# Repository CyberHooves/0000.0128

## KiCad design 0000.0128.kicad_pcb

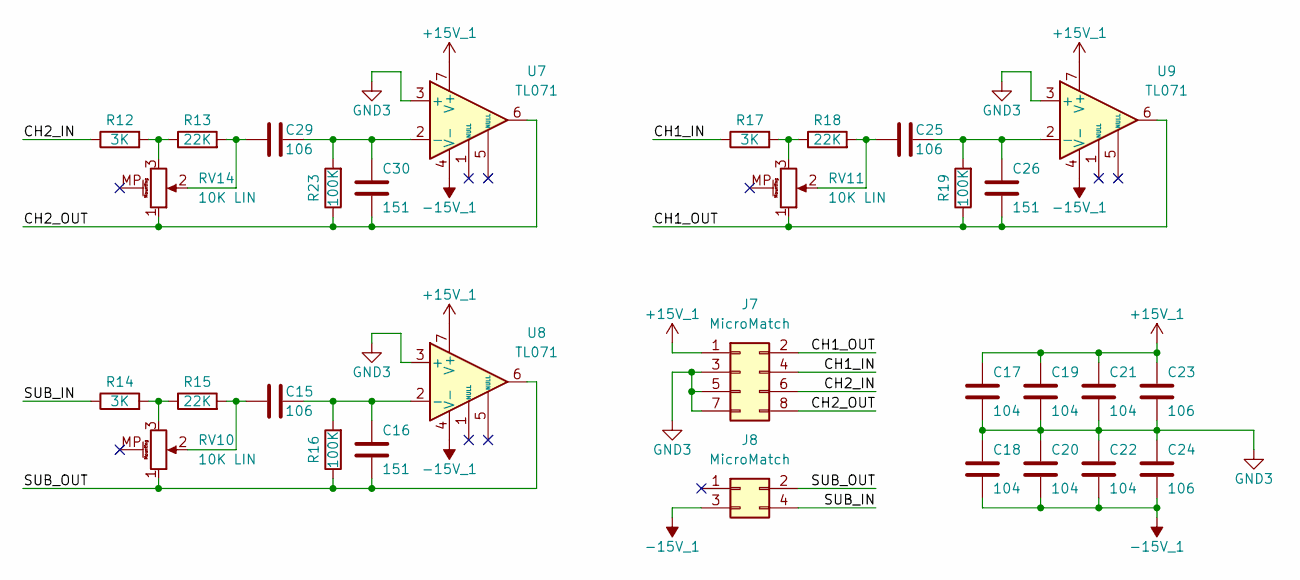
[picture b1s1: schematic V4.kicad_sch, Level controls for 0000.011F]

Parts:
C15, C23, C24, C25, C29: 106; C_1210_3225Metric
C16, C26, C30: 151; C_0805_2012Metric
C17, C18, C19, C20, C21, C22: 104; C_0805_2012Metric
J7: MicroMatch; TE_Micro-MaTch_215079-8_2x04_P1.27mm_Vertical
J8: MicroMatch; TE_Micro-MaTch_215079-4_2x02_P1.27mm_Vertical
R12, R14, R17: 3K; R_0805_2012Metric
R13, R15, R18: 22K; R_0805_2012Metric
R16, R19, R23: 100K; R_0805_2012Metric
RV10, RV11, RV14: 10K LIN; Potentiometer_Alps_RK09L_Single_Vertical
U7, U8, U9: TL071; SOIC-8_3.9x4.9mm_P1.27mm

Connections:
+15V_1: C17.1, C19.1, C21.1, C23.1, J7.1, U7.7 (V+), U8.7 (V+), U9.7 (V+)
-15V_1: C18.2, C20.2, C22.2, C24.2, J8.3, U7.4 (V-), U8.4 (V-), U9.4 (V-)
/Variant 4/CH1_IN: J7.4, R17.1
/Variant 4/CH1_OUT: C26.2, J7.2, R19.1, RV11.1, U9.6
/Variant 4/CH2_IN: J7.6, R12.1
/Variant 4/CH2_OUT: C30.2, J7.8, R23.1, RV14.1, U7.6
/Variant 4/SUB_IN: J8.4, R14.1
/Variant 4/SUB_OUT: C16.2, J8.2, R16.1, RV10.1, U8.6
GND3: C17.2, C18.1, C19.2, C20.1, C21.2, C22.1, C23.2, C24.1, J7.3, J7.5, J7.7, U7.3 (+), U8.3 (+), U9.3 (+)
unnamed: C15.1, R15.2, RV10.2
unnamed: C25.1, R18.2, RV11.2
unnamed: C29.1, R13.2, RV14.2
unnamed: R12.2, R13.1, RV14.3
unnamed: R14.2, R15.1, RV10.3
unnamed: R17.2, R18.1, RV11.3
unnamed: C29.2, C30.1, R23.2, U7.2 (-)
unnamed: C15.2, C16.1, R16.2, U8.2 (-)
unnamed: C25.2, C26.1, R19.2, U9.2 (-)

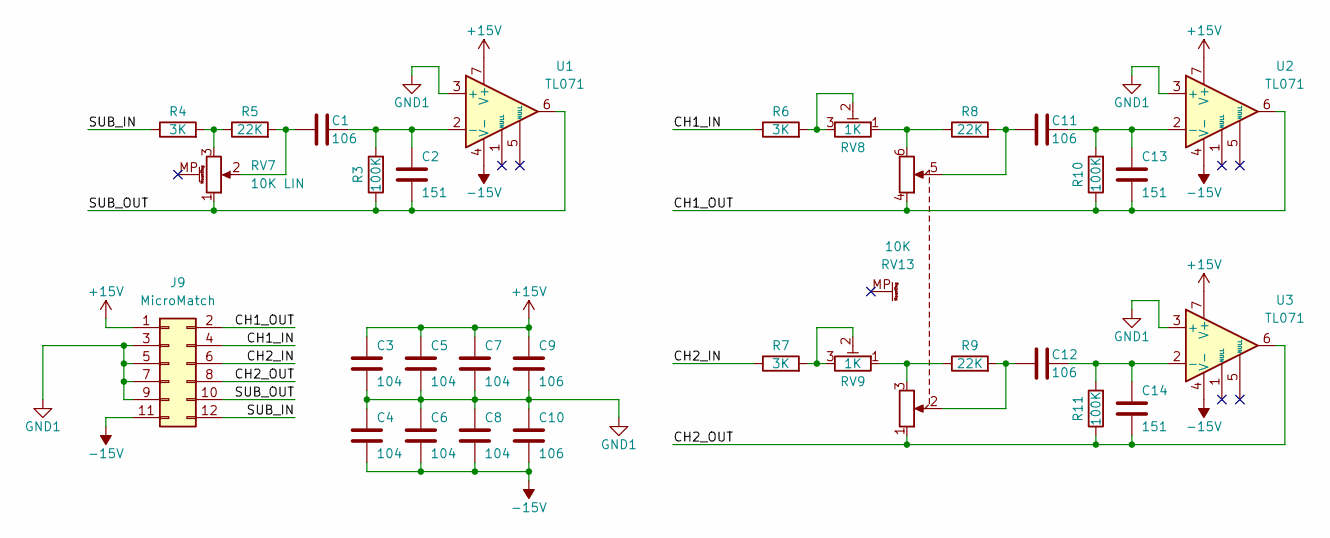
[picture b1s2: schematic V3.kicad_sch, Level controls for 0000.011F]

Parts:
C1, C9, C10, C11, C12: 106; C_1210_3225Metric
C2, C13, C14: 151; C_0805_2012Metric
C3, C4, C5, C6, C7, C8: 104; C_0805_2012Metric
J9: MicroMatch; TE_Micro-MaTch_1-215079-2_2x06_P1.27mm_Vertical
R3, R10, R11: 100K; R_0805_2012Metric
R4, R6, R7: 3K; R_0805_2012Metric
R5, R8, R9: 22K; R_0805_2012Metric
RV7: 10K LIN; Potentiometer_Alps_RK09L_Single_Vertical
RV8, RV9: 1K; Potentiometer_Bourns_3362P_Vertical
RV13: 10K; Potentiometer_Alps_RK09L_Double_Vertical
U1, U2, U3: TL071; SOIC-8_3.9x4.9mm_P1.27mm

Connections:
+15V: C3.1, C5.1, C7.1, C9.1, J9.1, U1.7 (V+), U2.7 (V+), U3.7 (V+)
-15V: C4.2, C6.2, C8.2, C10.2, J9.11, U1.4 (V-), U2.4 (V-), U3.4 (V-)
/Variant 3/CH1_IN: J9.4, R6.1
/Variant 3/CH1_OUT: C13.2, J9.2, R10.1, RV13.4, U2.6
/Variant 3/CH2_IN: J9.6, R7.1
/Variant 3/CH2_OUT: C14.2, J9.8, R11.1, RV13.1, U3.6
/Variant 3/SUB_IN: J9.12, R4.1
/Variant 3/SUB_OUT: C2.2, J9.10, R3.1, RV7.1, U1.6
GND1: C3.2, C4.1, C5.2, C6.1, C7.2, C8.1, C9.2, C10.1, J9.3, J9.5, J9.7, J9.9, U1.3 (+), U2.3 (+), U3.3 (+)
unnamed: C1.1, R5.2, RV7.2
unnamed: C11.1, R8.2, RV13.5
unnamed: C12.1, R9.2, RV13.2
unnamed: R4.2, R5.1, RV7.3
unnamed: R6.2, RV8.2, RV8.3
unnamed: R7.2, RV9.2, RV9.3
unnamed: R8.1, RV8.1, RV13.6
unnamed: R9.1, RV9.1, RV13.3
unnamed: C1.2, C2.1, R3.2, U1.2 (-)
unnamed: C11.2, C13.1, R10.2, U2.2 (-)
unnamed: C12.2, C14.1, R11.2, U3.2 (-)

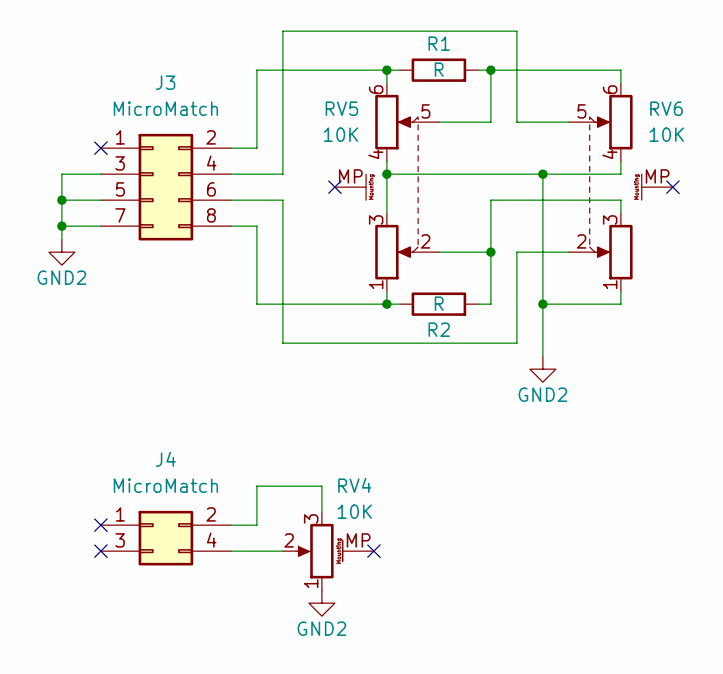
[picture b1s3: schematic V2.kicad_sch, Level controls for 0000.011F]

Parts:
J3: MicroMatch; TE_Micro-MaTch_215079-8_2x04_P1.27mm_Vertical
J4: MicroMatch; TE_Micro-MaTch_215079-4_2x02_P1.27mm_Vertical
R1, R2: R; R_0805_2012Metric
RV4: 10K; Potentiometer_Alps_RK09L_Single_Vertical
RV5, RV6: 10K; Potentiometer_Alps_RK09L_Double_Vertical

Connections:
GND2: J3.3, J3.5, J3.7, RV4.1, RV5.3, RV5.4, RV6.1, RV6.4
unnamed: J3.2, R1.1, RV5.6
unnamed: J3.4, RV6.5
unnamed: J3.6, RV6.2
unnamed: J3.8, R2.1, RV5.1
unnamed: J4.2, RV4.3
unnamed: J4.4, RV4.2
unnamed: R1.2, RV5.5, RV6.6
unnamed: R2.2, RV5.2, RV6.3

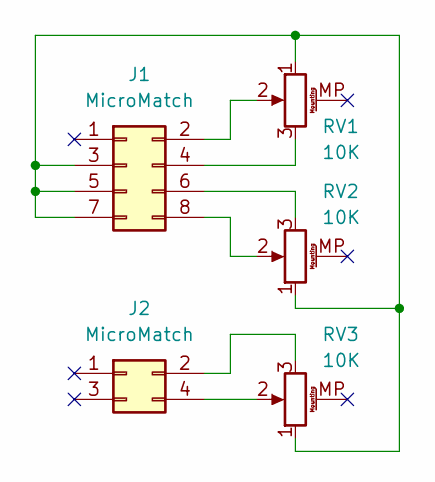
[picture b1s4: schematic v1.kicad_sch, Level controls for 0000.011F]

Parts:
J1: MicroMatch; TE_Micro-MaTch_215079-8_2x04_P1.27mm_Vertical
J2: MicroMatch; TE_Micro-MaTch_215079-4_2x02_P1.27mm_Vertical
RV1, RV2, RV3: 10K; Potentiometer_Alps_RK09L_Single_Vertical

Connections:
unnamed: J1.2, RV1.2
unnamed: J1.3, J1.5, J1.7, RV1.1, RV2.1, RV3.1
unnamed: J1.4, RV1.3
unnamed: J1.6, RV2.3
unnamed: J1.8, RV2.2
unnamed: J2.2, RV3.3
unnamed: J2.4, RV3.2

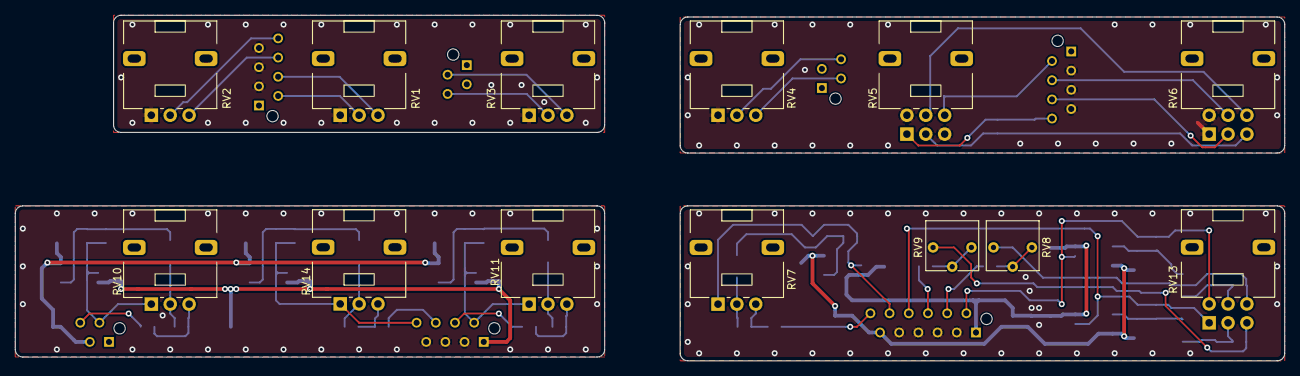
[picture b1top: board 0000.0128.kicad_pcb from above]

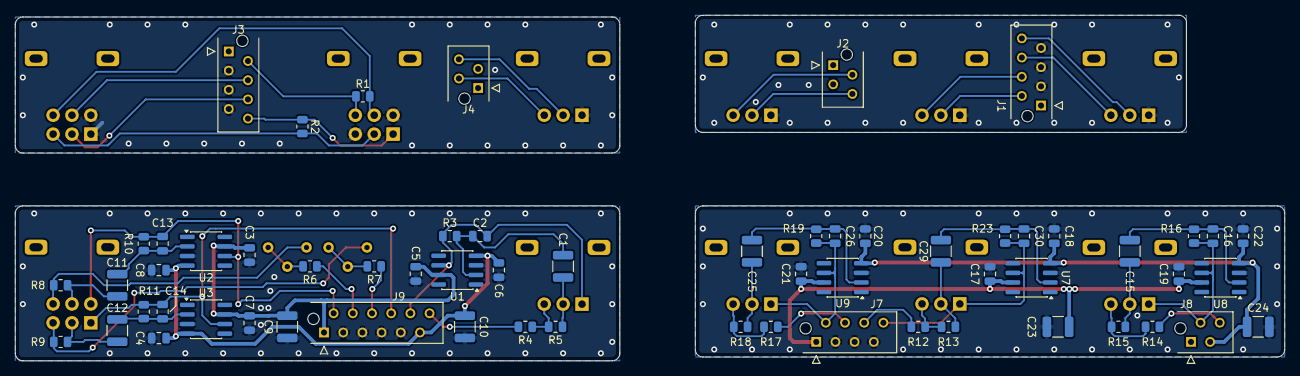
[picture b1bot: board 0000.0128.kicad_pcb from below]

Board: 2 copper layers, 168.0 x 45.7 mm, 74 parts (61 on the bottom side), 54 nets.

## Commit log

2025-08-25 Oops, all of the single gang pots were backwards - fixed.
2026-05-18 Active control topology changed to a single op-amp version.

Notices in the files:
0000.0128.kicad_pcb:
This is marked Creative Commons CC0 1.0
